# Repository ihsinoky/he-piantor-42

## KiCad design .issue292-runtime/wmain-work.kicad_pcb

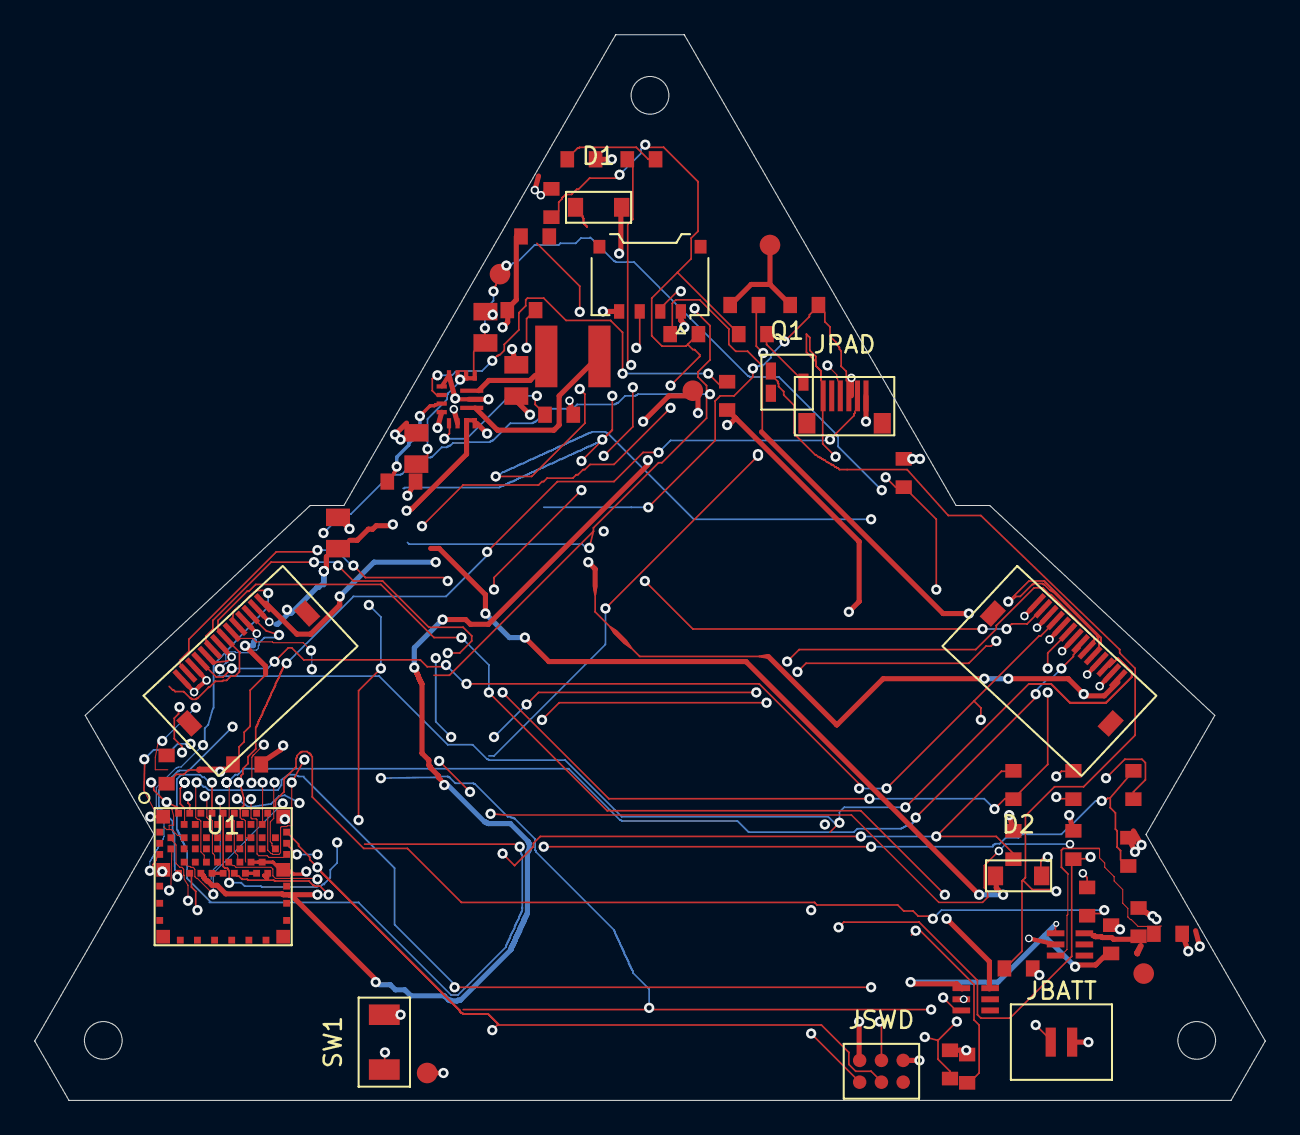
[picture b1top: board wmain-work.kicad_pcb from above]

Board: 4 copper layers, 71.8 x 62.2 mm, 55 parts (0 on the bottom side), 41 nets.

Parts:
CFA: 1nF; C_0603
CFB: 1nF; C_0603
CFC: 1nF; C_0603
CHIN: 1uF; C_0603
CHOUT: 1uF; C_0603
CIN1, CIN2: 22uF; C_0805
COUT1, COUT2: 22uF; C_0805
CPOUT: 1uF; C_0603
CVAUX: 1uF; C_0603
CVCC1: 1uF; C_0603
CVCC2: 100nF; C_0603
CVS: 10nF; C_0603
D1, D2: PMEG4020; SOD-123
DLED: LED green; R_0603
H1, H2, H3: NPTH 2.2mm; MountingHole_2.2mm
J2, J3: FH12-14S-0.5SH(55); FH12-14S-0.5SH
J4: 781710004 (Fly link); Pico-EZmate_781710004
JBATT: B2B-XH-A; GH2
JPAD: FH12-6S-class FFC; FFC6_0.5mm_land
JSWD: TC2030-IDC-NL; TC2030-IDC-NL_Pads
L1: 1.5uH XFL4020-152MEC; XFL4020
Q1: 2N7002; SOT-23
RFA: 6.8k; R_0603
RFB: 6.8k; R_0603
RFB1: 49.9k; R_0603
RFB2: 16.0k; R_0603
RFC: 6.8k; R_0603
RLED: 1k; R_0603
RPD1, RPD2, RPD3: 100k; R_0603
RPG: 100k; R_0603
RPU1, RPU2: 4.7k; R_0603
RRST: 10k; R_0603
RV1, RV2: 1M; R_0603
RVG: 100k; R_0603
RVPD: 100k; R_0603
SW1: TACT (bring-up); TACT_2pad
TP1: TP VIN_IN; TestPoint
TP2: TP SYS_3V3; TestPoint
TP3: TP HALL_3V3; TestPoint
TP4: TP PAD_3V3; TestPoint
TP5: TP GND; TestPoint
U1: ISP1807-LR
U2: TPS63070RNMR
U3, U4: TPS22919DCKR

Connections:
ADC_A: CFA.1, RFA.2, U1.48
ADC_B: CFB.1, RFB.2, U1.46
ADC_C: CFC.1, RFC.2, U1.42
ANT_LINK: U1.20, U1.22
BTN: SW1.1, U1.47
CONV_PG: RPG.2, U2.2
FB_3V3: RFB1.2, RFB2.1, U2.5
GND: CFA.2, CFB.2, CFC.2, CHIN.2, CHOUT.2, CIN1.2, CIN2.2, COUT1.2, COUT2.2, CPOUT.2, CVAUX.2, CVCC1.2, CVCC2.2, CVS.2, DLED.2, J2.1, J2.3, J2.5, J2.7, J2.11, J2.13, J3.1, J3.3, J3.5, J3.7, J3.11, J3.13, J4.4, JBATT.2, JPAD.2, JPAD.6, JSWD.5, Q1.2, RFB2.2, RPD1.2, RPD2.2, RPD3.2, RVPD.2, SW1.2, TP5.1, U1.1, U1.7, U1.14, U1.16, U1.18, U1.21, U1.23, U1.24, U1.25, U1.31, U2.1, U2.4, U2.6, U2.10, U2.15, U3.2, U4.2
HALL_3V3: CHOUT.1, J2.14, J3.14, TP3.1, U3.6
HALL_PWR_EN: RPD1.1, U1.15, U3.3
LED_A: DLED.1, RLED.2
LED_DRV: RLED.1, U1.56
MUX_A0: J2.12, J3.12, U1.5
MUX_A1: J2.10, J3.10, U1.6
MUX_A2: J2.9, J3.9, U1.9
MUX_EN0: J2.8, RPD2.1, U1.17
MUX_EN1: J3.8, RPD3.1, U1.19
MUX_OUT_A: J2.6, J3.6, RFA.1
MUX_OUT_B: J2.4, J3.4, RFB.1
MUX_OUT_C: J2.2, J3.2, RFC.1
PAD_3V3: CPOUT.1, JPAD.1, RPU1.1, RPU2.1, TP4.1, U4.6
PAD_DR: JPAD.5, U1.50
PAD_EN: U1.33, U4.3
PAD_SCL: JPAD.3, RPU1.2, U1.3
PAD_SDA: JPAD.4, RPU2.2, U1.32
RESET_N: JSWD.3, RRST.2, U1.13
SWDCLK: JSWD.4, U1.30
SWDIO: JSWD.2, U1.28
SW_A: L1.1, U2.11
SW_B: L1.2, U2.9
SYS_3V3: CHIN.1, COUT1.1, COUT2.1, CVCC1.1, CVCC2.1, JSWD.1, RFB1.1, RPG.1, RRST.1, TP2.1, U1.26, U2.7, U2.8, U3.1, U4.1
USB_DM: J4.2, U1.10
USB_DP: J4.3, U1.8
VAUX: CVAUX.1, U2.3
VBAT+: D2.2, JBATT.1, RV1.1
VBAT_DRAIN: Q1.3, RV2.2
VBAT_GATE: Q1.1, RVG.2, RVPD.1
VBAT_GATE_M: RVG.1, U1.27
VBAT_SENSE: CVS.1, RV1.2, RV2.1, U1.40
VBUS: D1.2, J4.1, U1.12
VIN_IN: CIN1.1, CIN2.1, D1.1, D2.1, TP1.1, U2.12, U2.13, U2.14

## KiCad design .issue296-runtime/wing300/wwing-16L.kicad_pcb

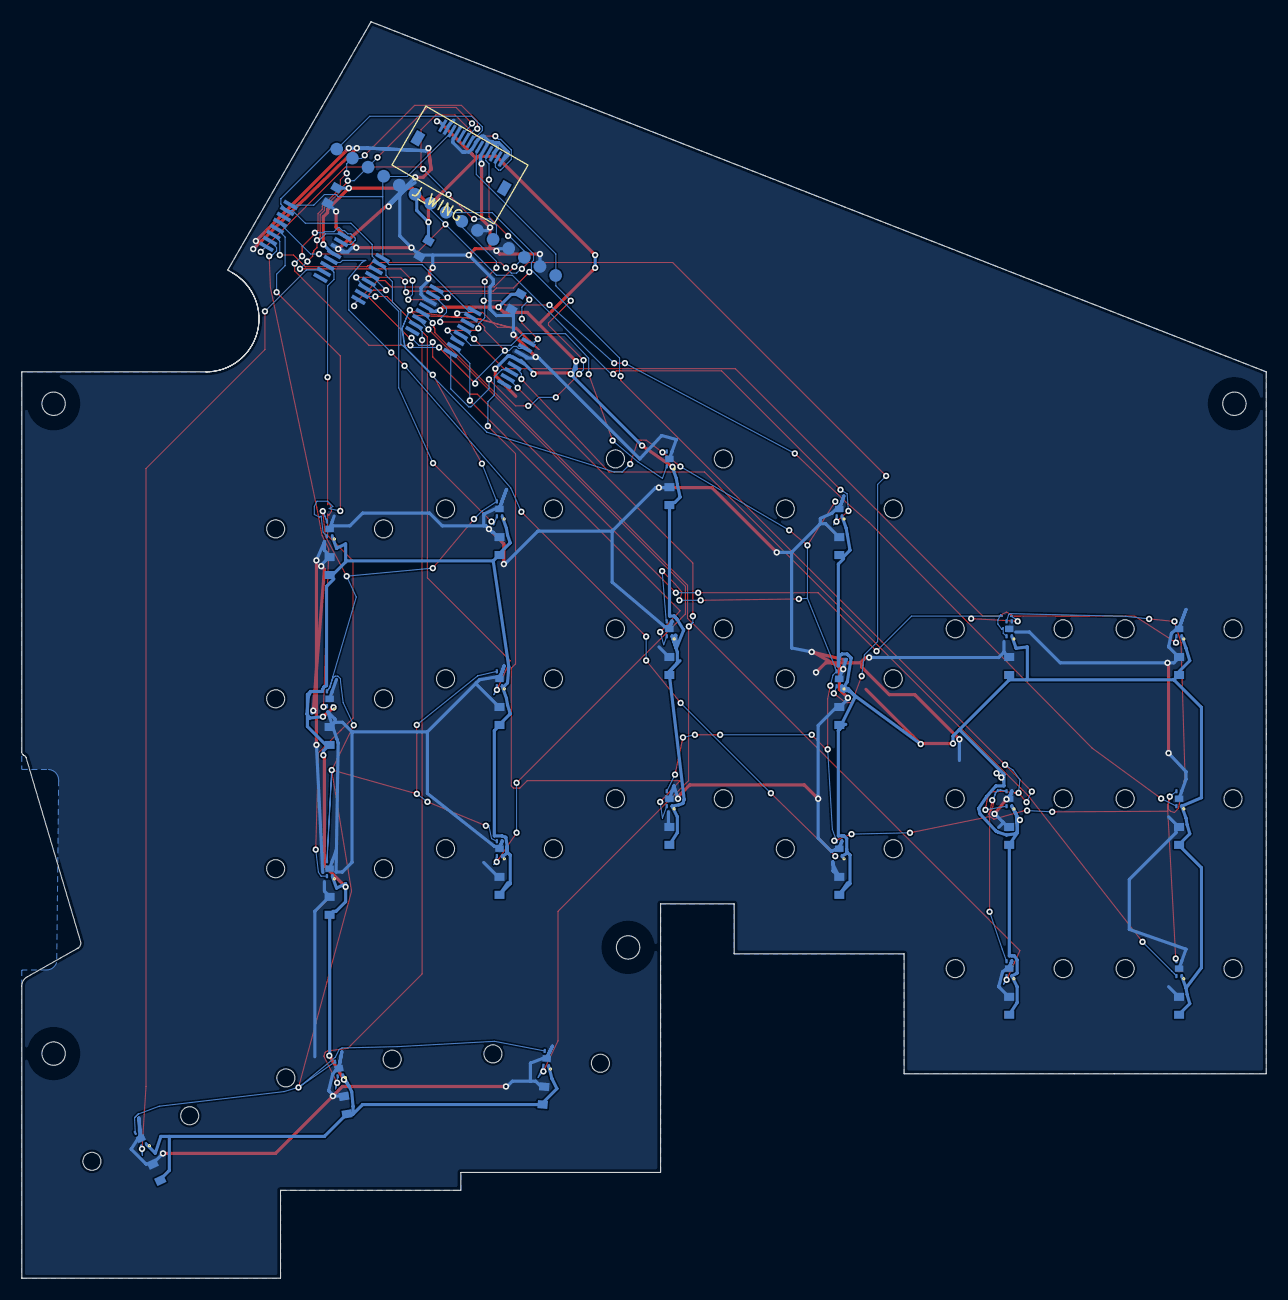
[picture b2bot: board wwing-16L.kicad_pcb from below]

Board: 2 copper layers, 117.2 x 118.3 mm, 110 parts (64 on the bottom side), 30 nets.

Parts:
C_HA0, C_HA1, C_HA2, C_HA3, C_HA4, C_HA5, C_HA6: GRM188R71C104KA01D; capacitor
C_HB0, C_HB1, C_HB2, C_HB3, C_HB4, C_HB5, C_HB6: GRM188R71C104KA01D; capacitor
C_HC0, C_HC1, C_HC2, C_HC3, C_HC4, C_HC5, C_HC6: GRM188R71C104KA01D; capacitor
C_MUX_A: GRM188R71C104KA01D; capacitor
C_MUX_B: GRM188R71C104KA01D; capacitor
C_MUX_C: GRM188R71C104KA01D; capacitor
H1, H2, H3, H4: NPTH_2.2; NPTH
J_WING: FH12-14S-0.5SH(55); Hirose_FH12-14S-0.5SH_1x14-1MP_P0.50mm_Horizontal
MH_1_1, MH_1_2, MH_2_1, MH_2_2, MH_3_1, MH_3_2, MH_4_1, MH_4_2, MH_5_1, MH_5_2, MH_6_1, MH_6_2, MH_7_1, MH_7_2, MH_8_1, MH_8_2, MH_9_1, MH_9_2, MH_10_1, MH_10_2, MH_11_1, MH_11_2, MH_12_1, MH_12_2, MH_13_1, MH_13_2, MH_14_1, MH_14_2, MH_15_1, MH_15_2, MH_16_1, MH_16_2, MH_17_1, MH_17_2, MH_18_1, MH_18_2, MH_19_1, MH_19_2, MH_20_1, MH_20_2, MH_21_1, MH_21_2: NPTH_1.7; NPTH
TP_H_CTR_RAW: PCB_PAD_1.2MM; testpoint
TP_H_DIAG_RAW: PCB_PAD_1.2MM; testpoint
TP_H_N_RAW: PCB_PAD_1.2MM; testpoint
TP_W_A0, TP_W_A1, TP_W_A2: PCB_PAD_1.2MM; testpoint
TP_W_EN: PCB_PAD_1.2MM; testpoint
TP_W_GND: PCB_PAD_1.2MM; testpoint
TP_W_GND_A: PCB_PAD_1.2MM; testpoint
TP_W_GND_B: PCB_PAD_1.2MM; testpoint
TP_W_GND_C: PCB_PAD_1.2MM; testpoint
TP_W_H3V3: PCB_PAD_1.2MM; testpoint
TP_W_MUXA: PCB_PAD_1.2MM; testpoint
TP_W_MUXB: PCB_PAD_1.2MM; testpoint
TP_W_MUXC: PCB_PAD_1.2MM; testpoint
U_HA0, U_HA1, U_HA2, U_HA3, U_HA4, U_HA5, U_HA6: TMAG5253BA3IQDMRR; TMAG5253BA3_X2SON-4
U_HB0, U_HB1, U_HB2, U_HB3, U_HB4, U_HB5, U_HB6: TMAG5253BA3IQDMRR; TMAG5253BA3_X2SON-4
U_HC0, U_HC1, U_HC2, U_HC3, U_HC4, U_HC5, U_HC6: TMAG5253BA3IQDMRR; TMAG5253BA3_X2SON-4
U_MUX_A: TMUX1208PWR; mux
U_MUX_B: TMUX1208PWR; mux
U_MUX_C: TMUX1208PWR; mux

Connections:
GND: C_HA0.2, C_HA1.2, C_HA2.2, C_HA3.2, C_HA4.2, C_HA5.2, C_HA6.2, C_HB0.2, C_HB1.2, C_HB2.2, C_HB3.2, C_HB4.2, C_HB5.2, C_HB6.2, C_HC0.2, C_HC1.2, C_HC2.2, C_HC3.2, C_HC4.2, C_HC5.2, C_HC6.2, C_MUX_A.2, C_MUX_B.2, C_MUX_C.2, J_WING.2, J_WING.4, J_WING.8, J_WING.10, J_WING.12, J_WING.14, TP_W_GND.1, TP_W_GND_A.1, TP_W_GND_B.1, TP_W_GND_C.1, U_HA0.2, U_HA0.5, U_HA1.2, U_HA1.5, U_HA2.2, U_HA2.5, U_HA3.2, U_HA3.5, U_HA4.2, U_HA4.5, U_HA5.2, U_HA5.5, U_HA6.2, U_HA6.5, U_HB0.2, U_HB0.5, U_HB1.2, U_HB1.5, U_HB2.2, U_HB2.5, U_HB3.2, U_HB3.5, U_HB4.2, U_HB4.5, U_HB5.2, U_HB5.5, U_HB6.2, U_HB6.5, U_HC0.2, U_HC0.5, U_HC1.2, U_HC1.5, U_HC2.2, U_HC2.5, U_HC3.2, U_HC3.5, U_HC4.2, U_HC4.5, U_HC5.2, U_HC5.5, U_HC6.2, U_HC6.5, U_MUX_A.14, U_MUX_B.14, U_MUX_C.14
HALL_3V3: C_HA0.1, C_HA1.1, C_HA2.1, C_HA3.1, C_HA4.1, C_HA5.1, C_HA6.1, C_HB0.1, C_HB1.1, C_HB2.1, C_HB3.1, C_HB4.1, C_HB5.1, C_HB6.1, C_HC0.1, C_HC1.1, C_HC2.1, C_HC3.1, C_HC4.1, C_HC5.1, C_HC6.1, C_MUX_A.1, C_MUX_B.1, C_MUX_C.1, J_WING.1, TP_W_H3V3.1, U_HA0.1, U_HA1.1, U_HA2.1, U_HA3.1, U_HA4.1, U_HA5.1, U_HA6.1, U_HB0.1, U_HB1.1, U_HB2.1, U_HB3.1, U_HB4.1, U_HB5.1, U_HB6.1, U_HC0.1, U_HC1.1, U_HC2.1, U_HC3.1, U_HC4.1, U_HC5.1, U_HC6.1, U_MUX_A.13, U_MUX_B.13, U_MUX_C.13
H_A0_RAW: U_HA0.4, U_MUX_A.4
H_A1_RAW: U_HA1.4, U_MUX_A.5
H_A2_RAW: TP_H_CTR_RAW.1, U_HA2.4, U_MUX_A.6
H_A3_RAW: U_HA3.4, U_MUX_A.7
H_A4_RAW: U_HA4.4, U_MUX_A.12
H_A5_RAW: U_HA5.4, U_MUX_A.11
H_A6_RAW: U_HA6.4, U_MUX_A.10
H_B0_RAW: U_HB0.4, U_MUX_B.4
H_B1_RAW: U_HB1.4, U_MUX_B.5
H_B2_RAW: TP_H_N_RAW.1, U_HB2.4, U_MUX_B.6
H_B3_RAW: U_HB3.4, U_MUX_B.7
H_B4_RAW: U_HB4.4, U_MUX_B.12
H_B5_RAW: U_HB5.4, U_MUX_B.11
H_B6_RAW: U_HB6.4, U_MUX_B.10
H_C0_RAW: TP_H_DIAG_RAW.1, U_HC0.4, U_MUX_C.4
H_C1_RAW: U_HC1.4, U_MUX_C.5
H_C2_RAW: U_HC2.4, U_MUX_C.6
H_C3_RAW: U_HC3.4, U_MUX_C.7
H_C4_RAW: U_HC4.4, U_MUX_C.12
H_C5_RAW: U_HC5.4, U_MUX_C.11
H_C6_RAW: U_HC6.4, U_MUX_C.10
MUX_A0: J_WING.3, TP_W_A0.1, U_MUX_A.1, U_MUX_B.1, U_MUX_C.1
MUX_A1: J_WING.5, TP_W_A1.1, U_MUX_A.16, U_MUX_B.16, U_MUX_C.16
MUX_A2: J_WING.6, TP_W_A2.1, U_MUX_A.15, U_MUX_B.15, U_MUX_C.15
MUX_OUT_A: J_WING.9, TP_W_MUXA.1, U_MUX_A.8
MUX_OUT_B: J_WING.11, TP_W_MUXB.1, U_MUX_B.8
MUX_OUT_C: J_WING.13, TP_W_MUXC.1, U_MUX_C.8
WING_EN: J_WING.7, TP_W_EN.1, U_HA0.3, U_HA1.3, U_HA2.3, U_HA3.3, U_HA4.3, U_HA5.3, U_HA6.3, U_HB0.3, U_HB1.3, U_HB2.3, U_HB3.3, U_HB4.3, U_HB5.3, U_HB6.3, U_HC0.3, U_HC1.3, U_HC2.3, U_HC3.3, U_HC4.3, U_HC5.3, U_HC6.3, U_MUX_A.2, U_MUX_B.2, U_MUX_C.2

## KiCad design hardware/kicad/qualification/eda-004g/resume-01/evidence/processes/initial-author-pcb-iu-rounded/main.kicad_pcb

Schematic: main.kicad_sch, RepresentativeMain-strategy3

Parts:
C1: 15pF; C1
C2: 15pF; C2
C3: 100nF; C3
C4: 100nF; C4
C5: 100nF; C5
C6: 100nF; C6
C7: 100nF; C7
C8: 100nF; C8
C9: 100nF; C9
C10: 100nF; C10
C11: 100nF; C11
C12: 1uF; C12
C13: 1uF; C13
C14: 10uF; C14
C15: 100nF; C15
C16: 1uF; C16
C17: 1uF; C17
C18: 1uF; C18
C19: 1uF; C19
C20: 1nF; C20
C21: 1nF; C21
C22: 1nF; C22
J1: TYPE-C-31-M-12; J1
J2: BM14B-GHS-TBT(LF)(SN); J2
R1: 5.1k; R1
R2: 5.1k; R2
R3: 27; R3
R4: 27; R4
R5: 1k; R5
R6: 100k; R6
R7: 100k; R7
R8: 10k; R8
R9: 1k; R9
R10: 6.8k; R10
R11: 10k; R11
R12: 6.8k; R12
R13: 10k; R13
R14: 6.8k; R14
R15: 10k; R15
TP1: TestPoint; TP1
TP2: TestPoint; TP2
TP3: TestPoint; TP3
TP4: TestPoint; TP4
U1: RP2040; U1
U2: USBLC6-2SC6; U2
U3: W25Q16JVUXIQ; U3
U4: AP2112K-3.3TRG1; U4
U5: TPS22919DCKR; U5
Y1: ABM8-272-T3; Y1

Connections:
ADC_A: C20.1, R10.2, R11.1, U1.38 (GPIO26/ADC0)
ADC_B: C21.1, R12.2, R13.1, U1.39 (GPIO27/ADC1)
ADC_C: C22.1, R14.2, R15.1, U1.40 (GPIO28/ADC2)
CC1: J1.3 (CC1), R1.1
CC2: J1.10 (CC2), R2.1
GND: C1.2, C2.2, C3.2, C4.2, C5.2, C6.2, C7.2, C8.2, C9.2, C10.2, C11.2, C12.2, C13.2, C14.2, C15.2, C16.2, C17.2, C18.2, C19.2, C20.2, C21.2, C22.2, J1.1 (GND), J1.12 (GND), J1.13 (SHIELD), J2.2, J2.4, J2.8, J2.10, J2.12, J2.14, R1.2, R2.2, R6.2, R7.2, R11.2, R13.2, R15.2, U1.19 (TESTEN), U1.57 (GND), U2.2 (GND), U3.4 (GND), U4.2 (GND), U5.2 (GND), Y1.2 (G), Y1.4 (G)
HALL_5V: C19.1, J2.1, U5.6 (OUT)
HALL_PWR_EN: R7.1, U1.9 (GPIO7), U5.3 (ON)
MUX_A0: J2.3, U1.4 (GPIO2)
MUX_A1: J2.5, U1.5 (GPIO3)
MUX_A2: J2.6, U1.6 (GPIO4)
MUX_OUT_A: J2.9, R10.1
MUX_OUT_B: J2.11, R12.1
MUX_OUT_C: J2.13, R14.1
QSPI_SCLK: U1.52 (QSPI_SCLK), U3.6 (CLK)
QSPI_SD0: U1.53 (QSPI_SD0), U3.5 (DI(IO0))
QSPI_SD1: U1.55 (QSPI_SD1), U3.2 (DO(IO1))
QSPI_SD2: U1.54 (QSPI_SD2), U3.3 (~WP(IO2))
QSPI_SD3: U1.51 (QSPI_SD3), U3.7 (~HOLD(IO3))
QSPI_SS_FLASH: R5.2, TP4.1, U3.1 (~CS)
QSPI_SS_MCU: R5.1, U1.56 (~QSPI_SS)
RUN: R8.2, TP3.1, U1.26 (RUN)
SWCLK: TP2.1, U1.24 (SWCLK)
SWDIO: TP1.1, U1.25 (SWDIO)
USB_DM: R4.2, U1.46 (USB_DM)
USB_DM_CONN: J1.5 (D-), J1.8 (D-), U2.3 (I/O2)
USB_DM_ESD: R4.1, U2.4 (I/O2)
USB_DP: R3.2, U1.47 (USB_DP)
USB_DP_CONN: J1.4 (D+), J1.9 (D+), U2.1 (I/O1)
USB_DP_ESD: R3.1, U2.6 (I/O1)
V1V1: C11.1, C13.1, U1.23 (DVDD), U1.45 (VREG_VOUT), U1.50 (DVDD)
V3V3: C3.1, C4.1, C5.1, C6.1, C7.1, C8.1, C9.1, C10.1, C12.1, C14.1, C15.1, C17.1, R8.1, U1.1 (IOVDD), U1.10 (IOVDD), U1.22 (IOVDD), U1.33 (IOVDD), U1.42 (IOVDD), U1.43 (ADC_AVDD), U1.44 (VREG_VIN), U1.48 (USB_VDD), U1.49 (IOVDD), U3.8 (VCC), U4.5 (VOUT)
VBUS: C16.1, C18.1, J1.2 (VBUS), J1.11 (VBUS), U2.5 (VBUS), U4.1 (VIN), U4.3 (EN), U5.1 (IN)
WING_EN: J2.7, R6.1, U1.7 (GPIO5)
XIN: C1.1, U1.20 (XIN), Y1.1
XOUT: R9.2, U1.21 (XOUT)
XOUT_XTAL: C2.1, R9.1, Y1.3

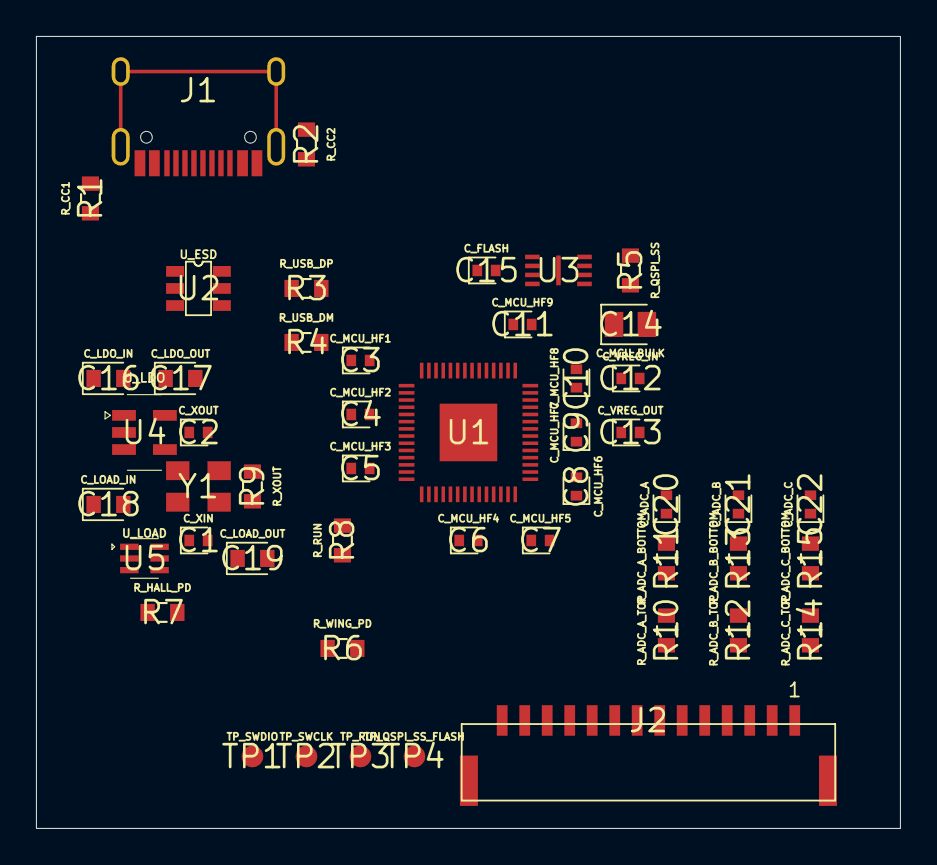
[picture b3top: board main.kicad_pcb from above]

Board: 2 copper layers, 48.0 x 44.0 mm, 49 parts (0 on the bottom side), 37 nets.
